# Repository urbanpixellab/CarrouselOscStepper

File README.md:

# Development

Install Arduino and Teensy software and open the sketch file with

    arduino CarouselOscStepper/CarouselOscStepper.ino &

# CarrouselOscStepper
* testwise two toggels on pin 6 and 7 for direction and go... only testwise for onlocation
* testwise nodstop on all microswitches
* added eagle 7.7 board and schematic
* added gerberfiles for the receiver motor part

## implemented
* receiving osc for target of stepper
* spinning to this position in loop per 10 steps, otherwise the moter gets stuck if i loop every step
* the motor checks self if hi is on target
* through this we can always send him a position and he goes as fast to this position

* multiplexing the 8 microswitches is working
* sending osc feedback if target reached or microswitch is pressed

## osc messages by now for control
* address "/input" followed by int for position in range 0-100
* teensy osc receives on port 10000 and sends on port 11000 to receive osc ip(master)

## teensy pin mapping
* final after pcb design
* 

## check for pcb making
https://www.pcbcreators.com/

## Some Thoughts about OSC messages
* the address is followed by 4 int values for the steppers 
* "/p" for position		
* "/c" for calibrate

* also maybe including the temp sensor to give information about the tempinside the box

## Some Links
* circuits ... are followinh
* https://github.com/R2D2-2017/R2D2-2017/wiki/NEMA17-stepper-motor-and-DRV8825
* https://lastminuteengineers.com/drv8825-stepper-motor-driver-arduino-tutorial/
* https://www.makerguides.com/drv8825-stepper-motor-driver-arduino-tutorial/
* https://github.com/CNMAT/OSC
* https://www.google.com/search?q=teensy+wiz820io&source=lnms&tbm=isch&sa=X&ved=0ahUKEwiooqeDwbfjAhVDDewKHfJNA8EQ_AUIECgB&biw=1487&bih=886#imgrc=dpOUuCkrrY9njM:
* https://forum.arduino.cc/index.php?topic=415724.0
* 
## by now we are using the easydriver v4 but it will be replaced by the drv8825
* another version from urbanpixellab https://github.com/urbanpixellab/ProtoDraai2019

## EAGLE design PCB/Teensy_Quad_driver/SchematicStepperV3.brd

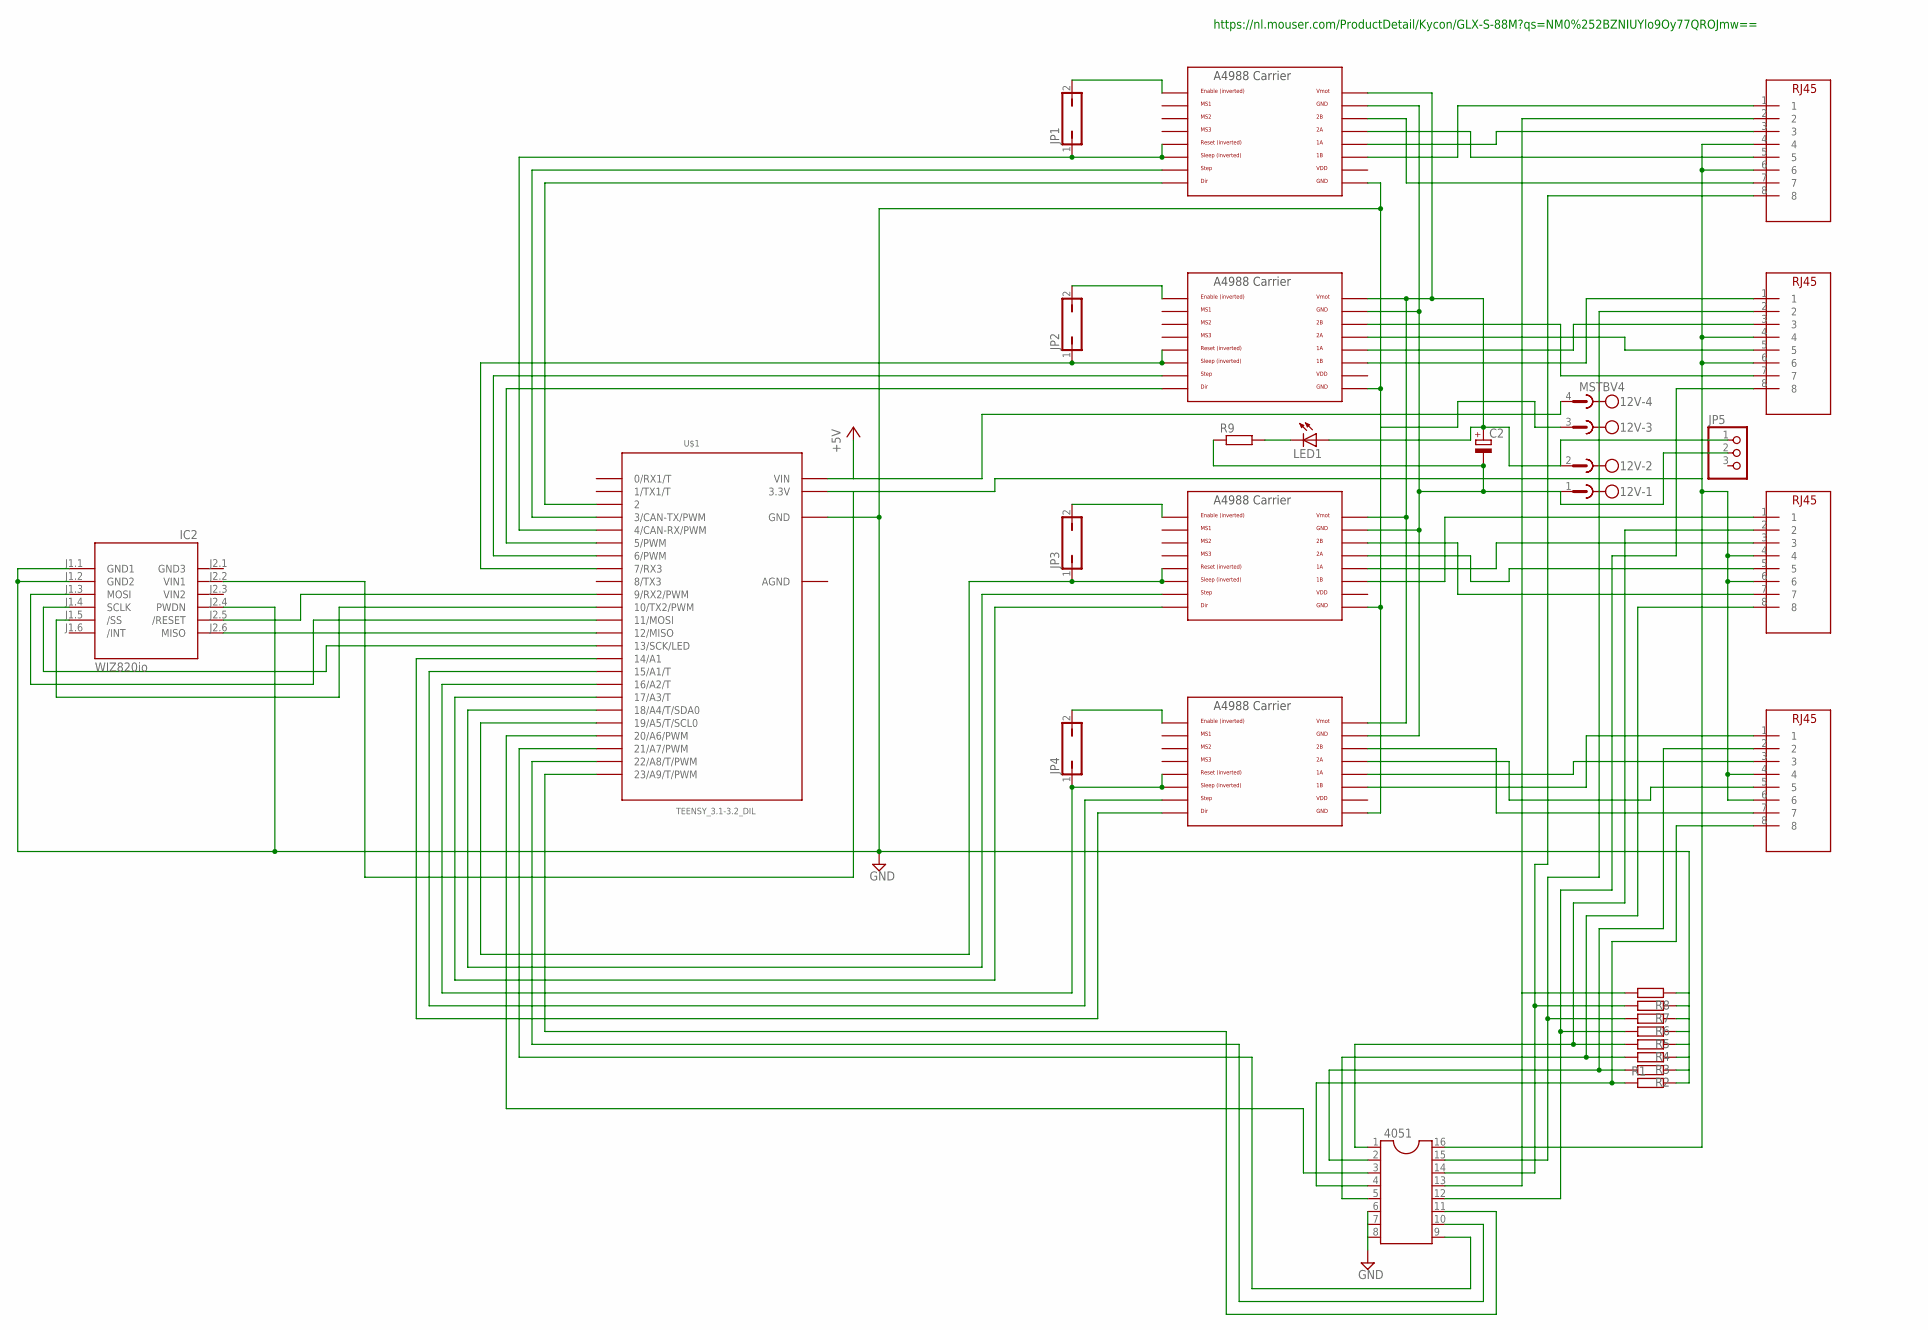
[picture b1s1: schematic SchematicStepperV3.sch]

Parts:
12V: MSTBV4
4051: DIL16
C2: CPOL-EUB45181B; B45181B
IC2: WIZ820io; WIZ820IO
JP1, JP2, JP3, JP4: JP1Q; JP1
JP5: PINHD-1X3; 1X03
LED1: LED_ELD260; LED_LD260
R1, R2, R3, R4, R5, R6, R7, R8, R9: R-EU_0309/10; 0309/10
U$1: TEENSY_3.1-3.2_DIL; TEENSY_3.0-3.2&LC_DIL
U$2, U$3, U$4, U$5: A4988BREAKOUT
WEIDMUELLER_RJ1, WEIDMUELLER_RJ2, WEIDMUELLER_RJ3, WEIDMUELLER_RJ4: WEIDMUELLER_RJ45

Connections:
4051: 4051.3, U$1.20/A6 (20/A6/PWM)
+5V: 12V.4, U$1.VIN
AGND: U$1.AGND
GND: 12V.3, 4051.6, 4051.7, 4051.8, IC2.J1.1 (GND1), IC2.J1.2 (GND2), IC2.J2.4 (PWDN), R1.2, R2.1, R3.1, R4.1, R5.1, R6.1, R7.1, R8.1, U$1.GND, U$2.GND, U$3.GND, U$4.GND, U$5.GND
GND3: IC2.J2.1 (GND3)
unnamed: JP2.1, U$1.7 (7/RX3), U$3.RST, U$3.SLP (SLEEP)
unnamed: 12V.1, C2.-, JP5.2, R9.1, U$2.GND_MOT, U$3.GND_MOT, U$4.GND_MOT, U$5.GND_MOT
unnamed: JP3.1, U$1.19/A5 (19/A5/T/SCL0), U$4.RST, U$4.SLP (SLEEP)
unnamed: JP1.1, U$1.4 (4/CAN-RX/PWM), U$2.RST, U$2.SLP (SLEEP)
unnamed: U$1.2, U$2.DIR
unnamed: U$1.3 (3/CAN-TX/PWM), U$2.STEP
unnamed: U$1.5 (5/PWM), U$3.DIR
unnamed: U$1.6 (6/PWM), U$3.STEP
unnamed: U$1.17/A3 (17/A3/T), U$4.DIR
unnamed: U$1.18/A4 (18/A4/T/SDA0), U$4.STEP
unnamed: 12V.2, C2.+, JP5.1, LED1.A, U$2.VMOT, U$3.VMOT, U$4.VMOT, U$5.VMOT
unnamed: JP4.1, U$1.16/A2 (16/A2/T), U$5.RST, U$5.SLP (SLEEP)
unnamed: U$3.1A, WEIDMUELLER_RJ2.3
unnamed: U$2.2B, WEIDMUELLER_RJ1.7
unnamed: U$2.1A, WEIDMUELLER_RJ1.3
unnamed: 4051.16, IC2.J2.2 (VIN1), U$1.3.3V, WEIDMUELLER_RJ1.4, WEIDMUELLER_RJ1.6, WEIDMUELLER_RJ2.4, WEIDMUELLER_RJ2.6, WEIDMUELLER_RJ3.4, WEIDMUELLER_RJ3.6, WEIDMUELLER_RJ4.4, WEIDMUELLER_RJ4.6
unnamed: IC2.J2.5 (/RESET), U$1.9 (9/RX2/PWM)
unnamed: IC2.J2.6 (MISO), U$1.12 (12/MISO)
unnamed: IC2.J1.3 (MOSI), U$1.11 (11/MOSI)
unnamed: IC2.J1.4 (SCLK), U$1.13 (13/SCK/LED)
unnamed: IC2.J1.5 (/SS), U$1.10 (10/TX2/PWM)
unnamed: U$2.2A, WEIDMUELLER_RJ1.5
unnamed: U$3.2A, WEIDMUELLER_RJ2.5
unnamed: U$3.2B, WEIDMUELLER_RJ2.7
unnamed: U$4.2A, WEIDMUELLER_RJ3.5
unnamed: U$3.1B, WEIDMUELLER_RJ2.1
unnamed: U$4.1A, WEIDMUELLER_RJ3.3
unnamed: U$4.2B, WEIDMUELLER_RJ3.7
unnamed: U$5.1A, WEIDMUELLER_RJ4.3
unnamed: U$4.1B, WEIDMUELLER_RJ3.1
unnamed: U$5.2B, WEIDMUELLER_RJ4.7
unnamed: U$5.2A, WEIDMUELLER_RJ4.5
unnamed: U$5.1B, WEIDMUELLER_RJ4.1
unnamed: LED1.K (C), R9.2
unnamed: JP1.2, U$2.EN
unnamed: JP2.2, U$3.EN
unnamed: JP3.2, U$4.EN
unnamed: JP4.2, U$5.EN
unnamed: 4051.9, U$1.21/A7 (21/A7/PWM)
unnamed: 4051.13, R8.2, WEIDMUELLER_RJ1.2
unnamed: 4051.10, U$1.22/A8 (22/A8/T/PWM)
unnamed: 4051.11, U$1.23/A9 (23/A9/T/PWM)
unnamed: 4051.14, R7.2, WEIDMUELLER_RJ1.8
unnamed: 4051.15, R6.2, WEIDMUELLER_RJ2.2
unnamed: 4051.12, R5.2, WEIDMUELLER_RJ2.8
unnamed: 4051.1, R4.2, WEIDMUELLER_RJ3.2
unnamed: 4051.5, R3.2, WEIDMUELLER_RJ3.8
unnamed: 4051.2, R2.2, WEIDMUELLER_RJ4.2
unnamed: 4051.4, R1.1, WEIDMUELLER_RJ4.8
unnamed: U$2.1B, WEIDMUELLER_RJ1.1
unnamed: U$1.15/A1 (15/A1/T), U$5.STEP
unnamed: U$1.14/A0 (14/A1), U$5.DIR
VDD: U$2.VDD, U$3.VDD, U$4.VDD, U$5.VDD
VIN2: IC2.J2.3 (VIN2)

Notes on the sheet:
https://nl.mouser.com/ProductDetail/Kycon/GLX-S-88M?qs=NM0%252BZNIUYlo9Oy77QROJmw==

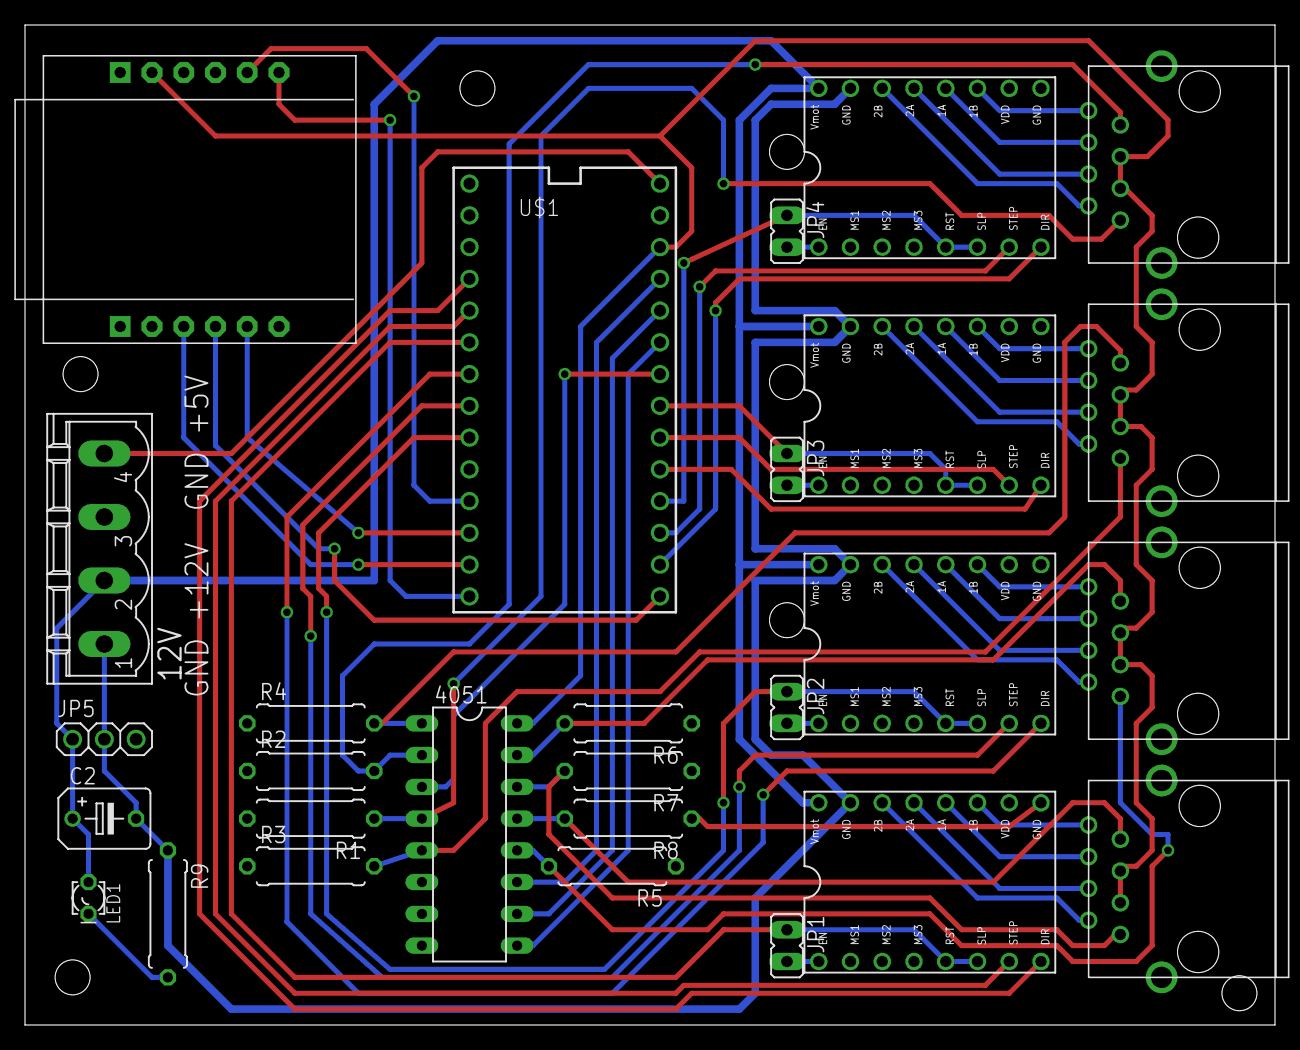
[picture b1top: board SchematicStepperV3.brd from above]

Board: 2 copper layers, 100.0 x 80.0 mm, 28 parts (0 on the bottom side), 56 nets.

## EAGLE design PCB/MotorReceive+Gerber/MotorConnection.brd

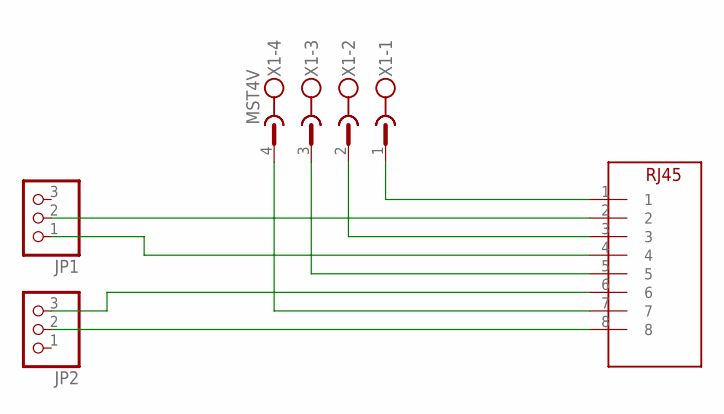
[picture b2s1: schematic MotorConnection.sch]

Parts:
JP1, JP2: PINHD-1X3; 1X03
WEIDMUELLER_RJ1: WEIDMUELLER_RJ45
X1: MST4V; MSTBV4

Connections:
unnamed: JP1.2, WEIDMUELLER_RJ1.2
unnamed: JP1.1, WEIDMUELLER_RJ1.4
unnamed: JP2.2, WEIDMUELLER_RJ1.8
unnamed: JP2.3, WEIDMUELLER_RJ1.6
unnamed: WEIDMUELLER_RJ1.1, X1.1
unnamed: WEIDMUELLER_RJ1.3, X1.2
unnamed: WEIDMUELLER_RJ1.5, X1.3
unnamed: WEIDMUELLER_RJ1.7, X1.4

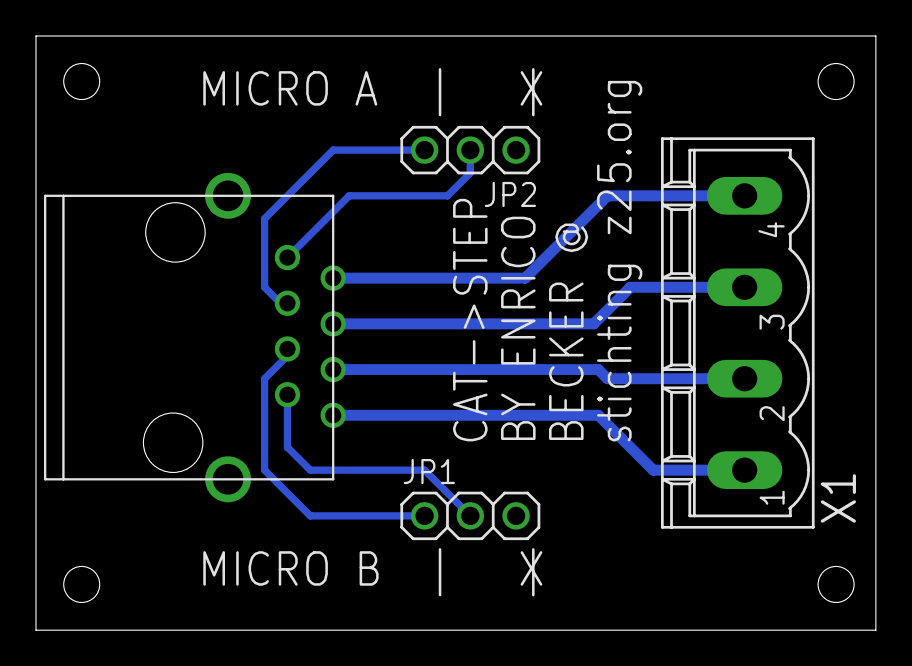
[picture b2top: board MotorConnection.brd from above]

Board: 2 copper layers, 46.7 x 33.0 mm, 4 parts (0 on the bottom side), 8 nets.

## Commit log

2019-07-16 added testfiles from latest drv8825 board and updated readme
2019-07-21 implemented simple stepper function, TODO must been inserted in the main loop see coments
2019-07-21 added step function in loop, totdo osc send when at target position
2019-07-21 implementedosc message onposition, must di this only once
2019-07-21 implemented only one feedback after target reached...mst been tested
2019-08-02 added osc feedback for microswitch and stepper on target
2019-08-16 added two buttons on 6 and 7 for on location test and removed network
2019-08-16 implemented not off onmicroswitches
2019-08-16 implemented multiplex microswitch stop
2019-08-16 serial print microswitch id
2019-08-16 enabled osc again
2019-08-19 added pcb eagle files
2019-08-19 added link for pcb in the netherlands to readme
2019-09-06 testversion
2019-09-09 first version with fixed gomax
